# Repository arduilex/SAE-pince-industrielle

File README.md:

# SAE-pince-industrielle
Instrumentation d'une pince pour un robot indutrielle Stäubli avec retour d'information sur l'état de la pince sur une IHM.

Vous pouvez lire le [Rapport](ressources/Rapport.pdf) et le [mannuel d'utilisation](ressources/manuel_utilisateur.pdf)

Ce projet a été réalisé dans le cadre d'une SAE de mon BUT GEII en première année à l'IUT de Mulhouse.

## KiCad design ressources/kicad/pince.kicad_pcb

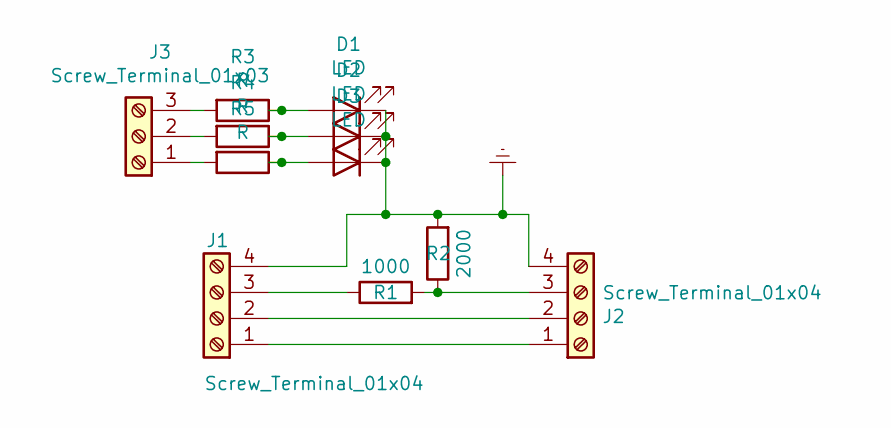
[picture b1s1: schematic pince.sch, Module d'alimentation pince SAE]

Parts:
D1, D2, D3: LED; LED_D8.0_mm_mod
J1: Screw_Terminal_01x04; TerminalBlock_bornier-4_P5.08mm
J2: Screw_Terminal_01x04; bornier_4_points
J3: Screw_Terminal_01x03; TerminalBlock_bornier-3_P5.08mm
R1: 1000; R
R2: 2000; R
R3, R4, R5: R

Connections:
Earth: D1.1 (K), D2.1 (K), D3.1 (K), J1.4, J2.4, R2.2
unnamed: D1.2 (A), R3.1
unnamed: D2.2 (A), R4.1
unnamed: D3.2 (A), R5.1
unnamed: J1.1, J2.1
unnamed: J1.2, J2.2
unnamed: J1.3, R1.1
unnamed: J2.3, R1.2, R2.1
unnamed: J3.1, R5.2
unnamed: J3.2, R4.2
unnamed: J3.3, R3.2

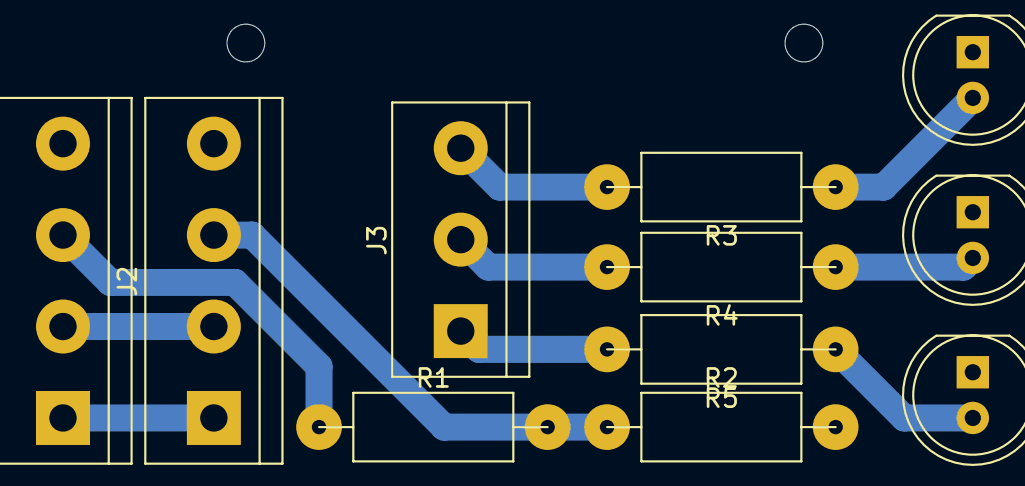
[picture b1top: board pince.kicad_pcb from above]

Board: 2 copper layers, 11 parts (0 on the bottom side), 11 nets.

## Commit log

2022-06-24 fichiers du projet actuelle
    Ces fichiers ne comprennent pas les commentaires et sont encore corrigeables
2022-06-24 test
2022-06-24 remettre le code d'avant
2022-06-24 séparation en dossier
2022-06-24 ajout d'un fichier 3D
2022-06-24 readme au bonne endroit
2022-06-24 readme modif
2022-06-24 ajout d'un redme
2022-06-24 nouveau dossier
2022-06-25 ajout de kicad et du manuel d'utilisation
2022-06-26 supprime fichier temp kicad
2022-06-26 CLDD
2022-06-26 ajout des fichiers 3D
2022-06-26 fichiers 3D
2022-06-27 update manual
2022-06-27 ajout rapport SAE
2022-07-04 ajout du rapport
